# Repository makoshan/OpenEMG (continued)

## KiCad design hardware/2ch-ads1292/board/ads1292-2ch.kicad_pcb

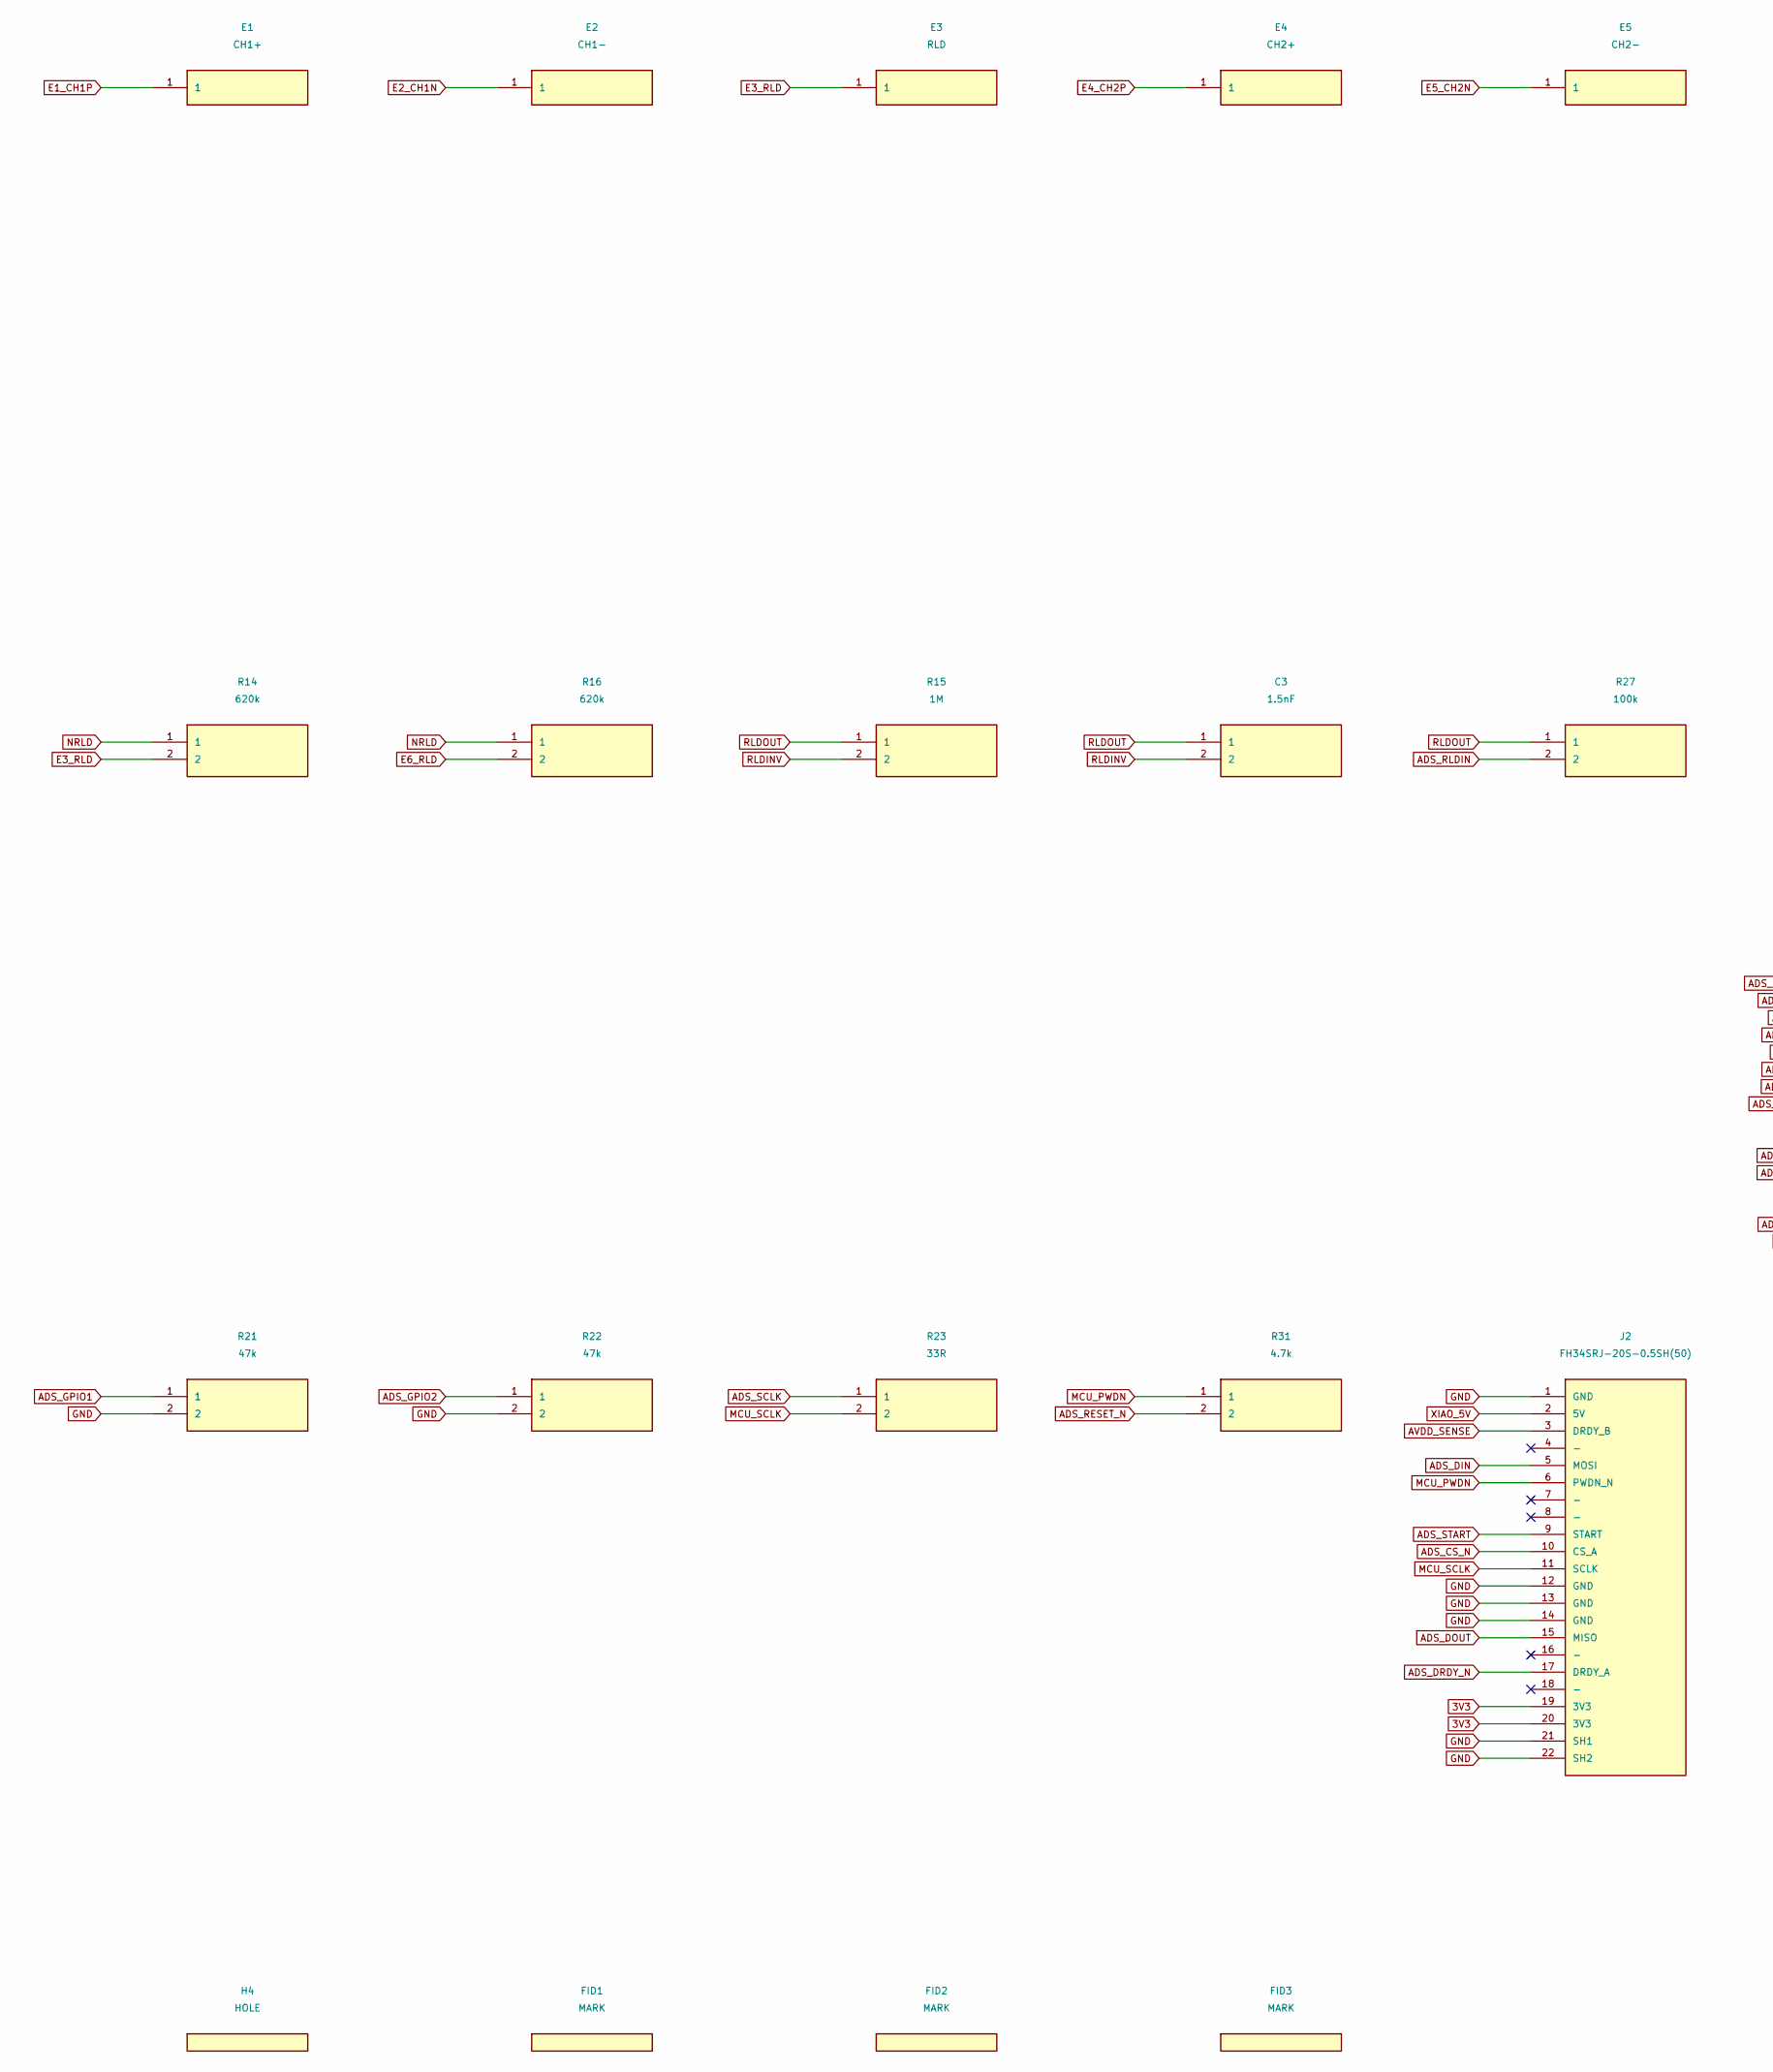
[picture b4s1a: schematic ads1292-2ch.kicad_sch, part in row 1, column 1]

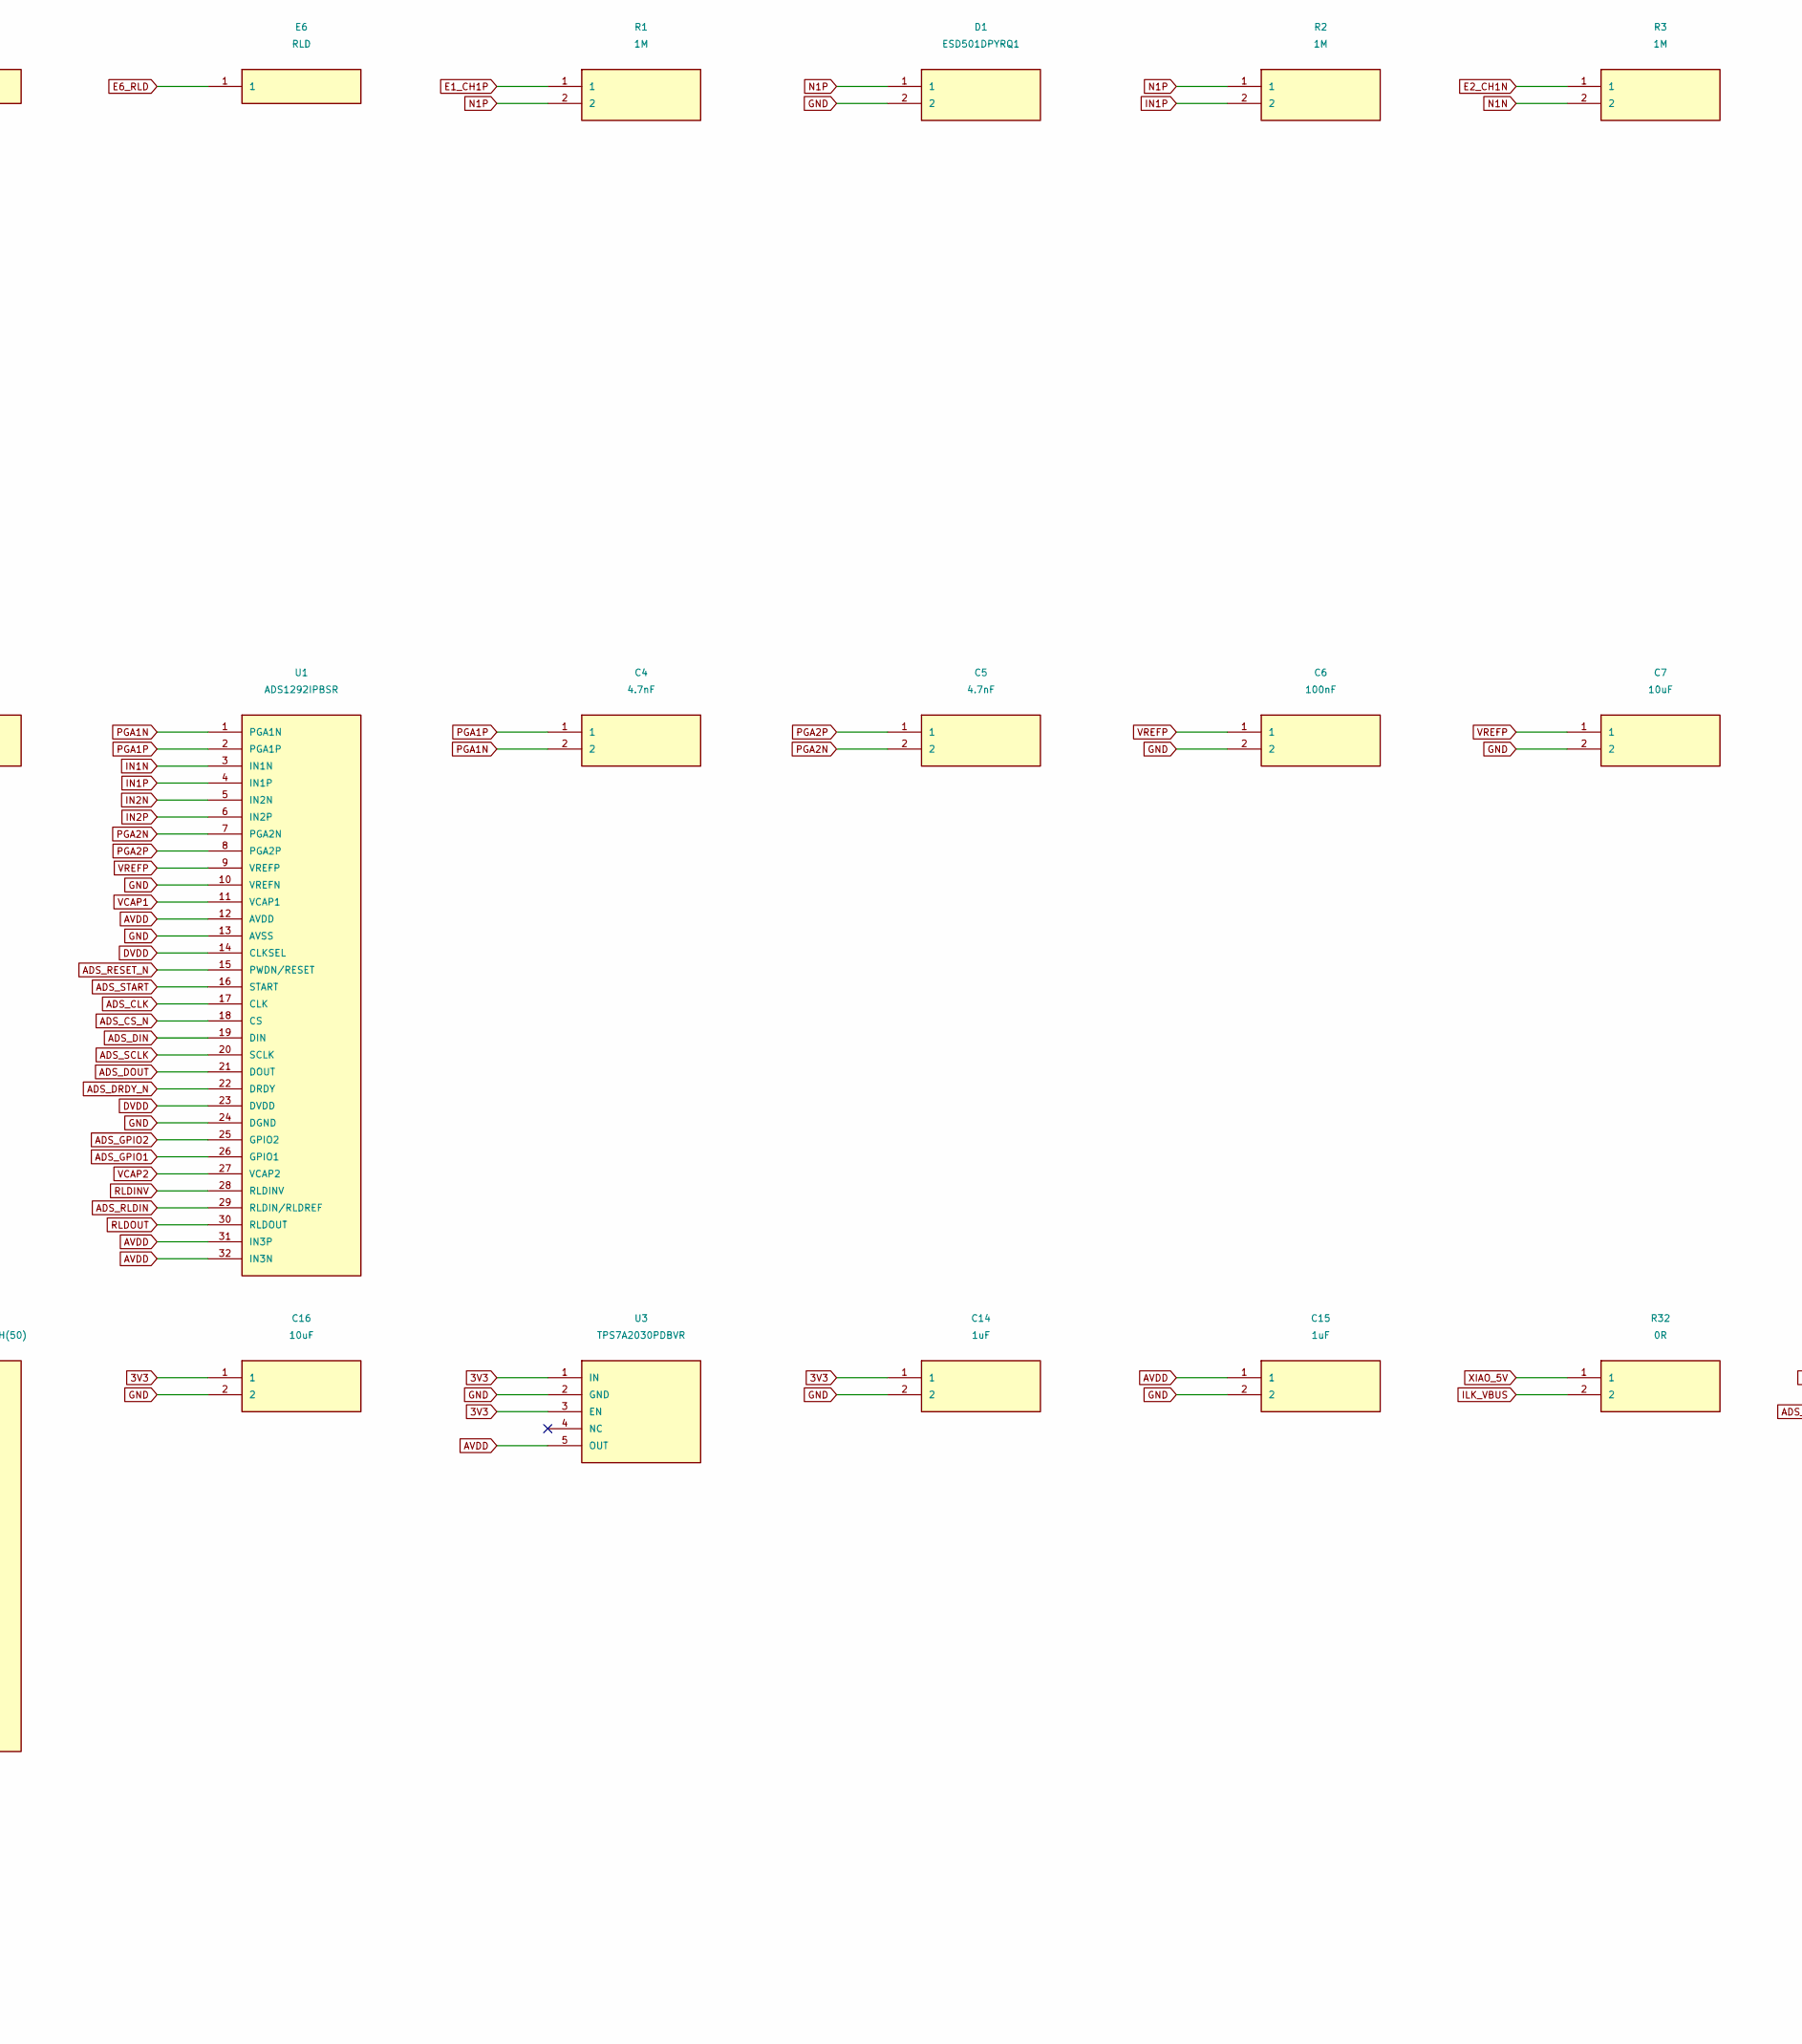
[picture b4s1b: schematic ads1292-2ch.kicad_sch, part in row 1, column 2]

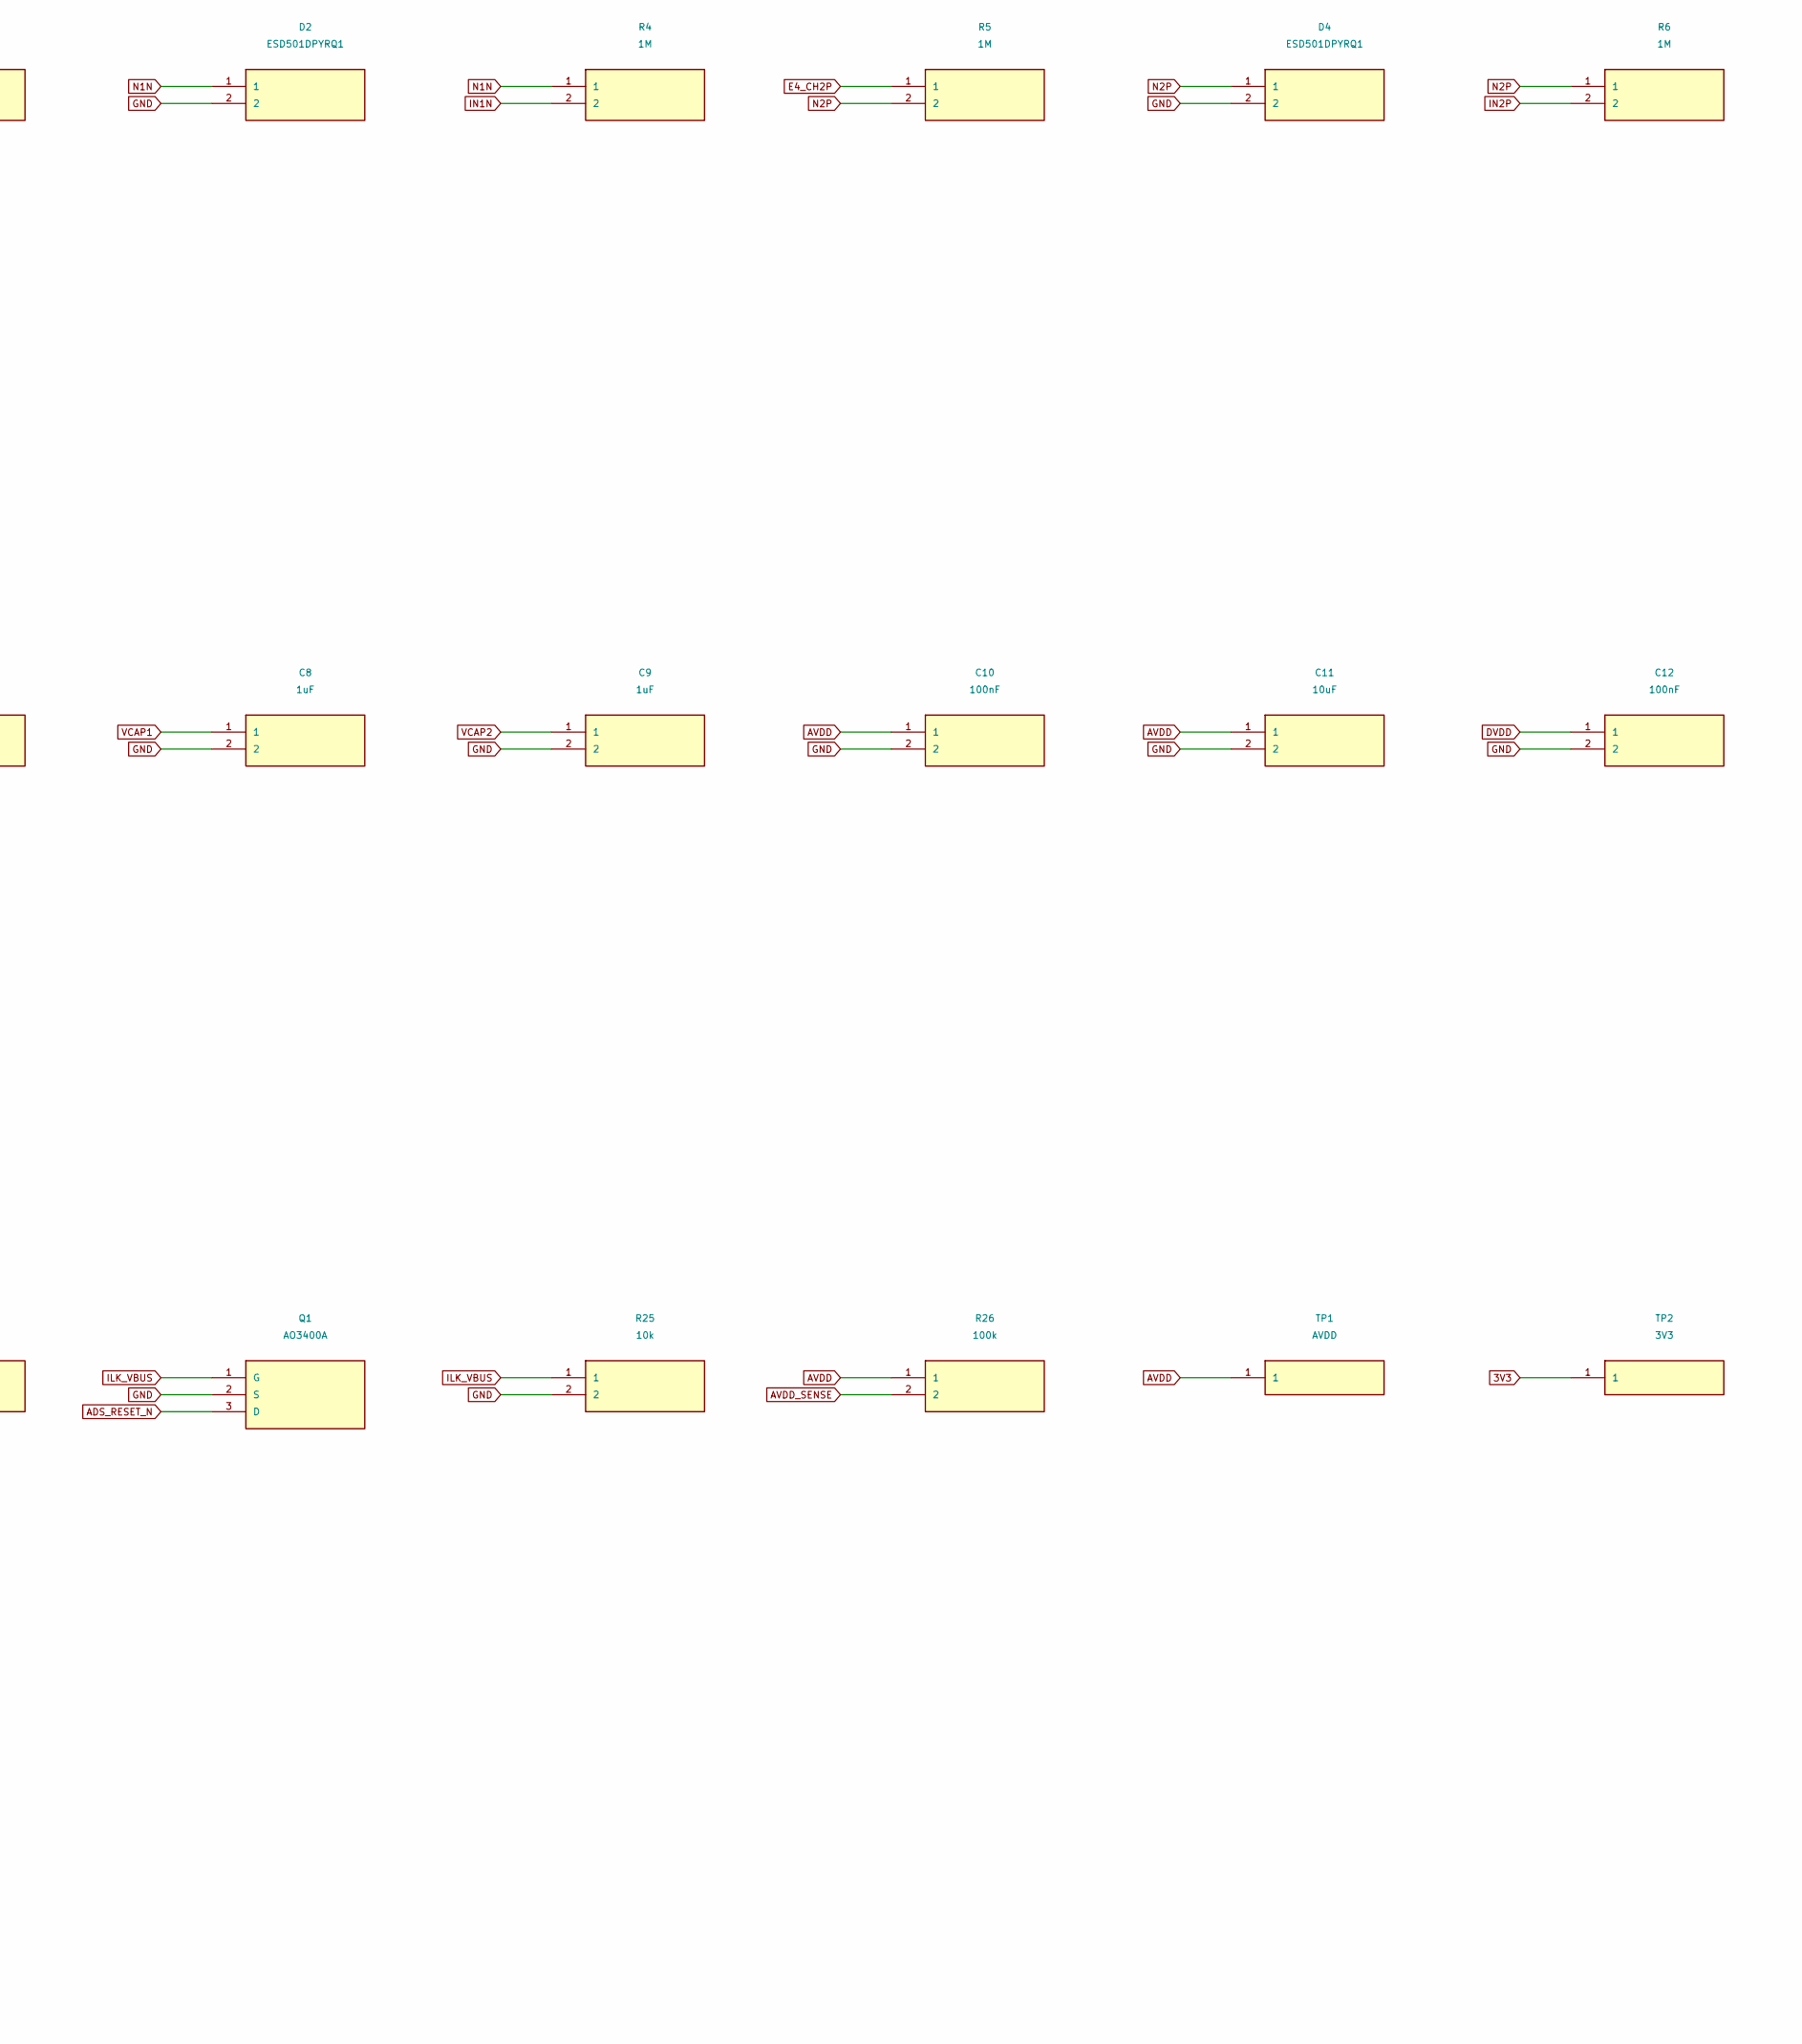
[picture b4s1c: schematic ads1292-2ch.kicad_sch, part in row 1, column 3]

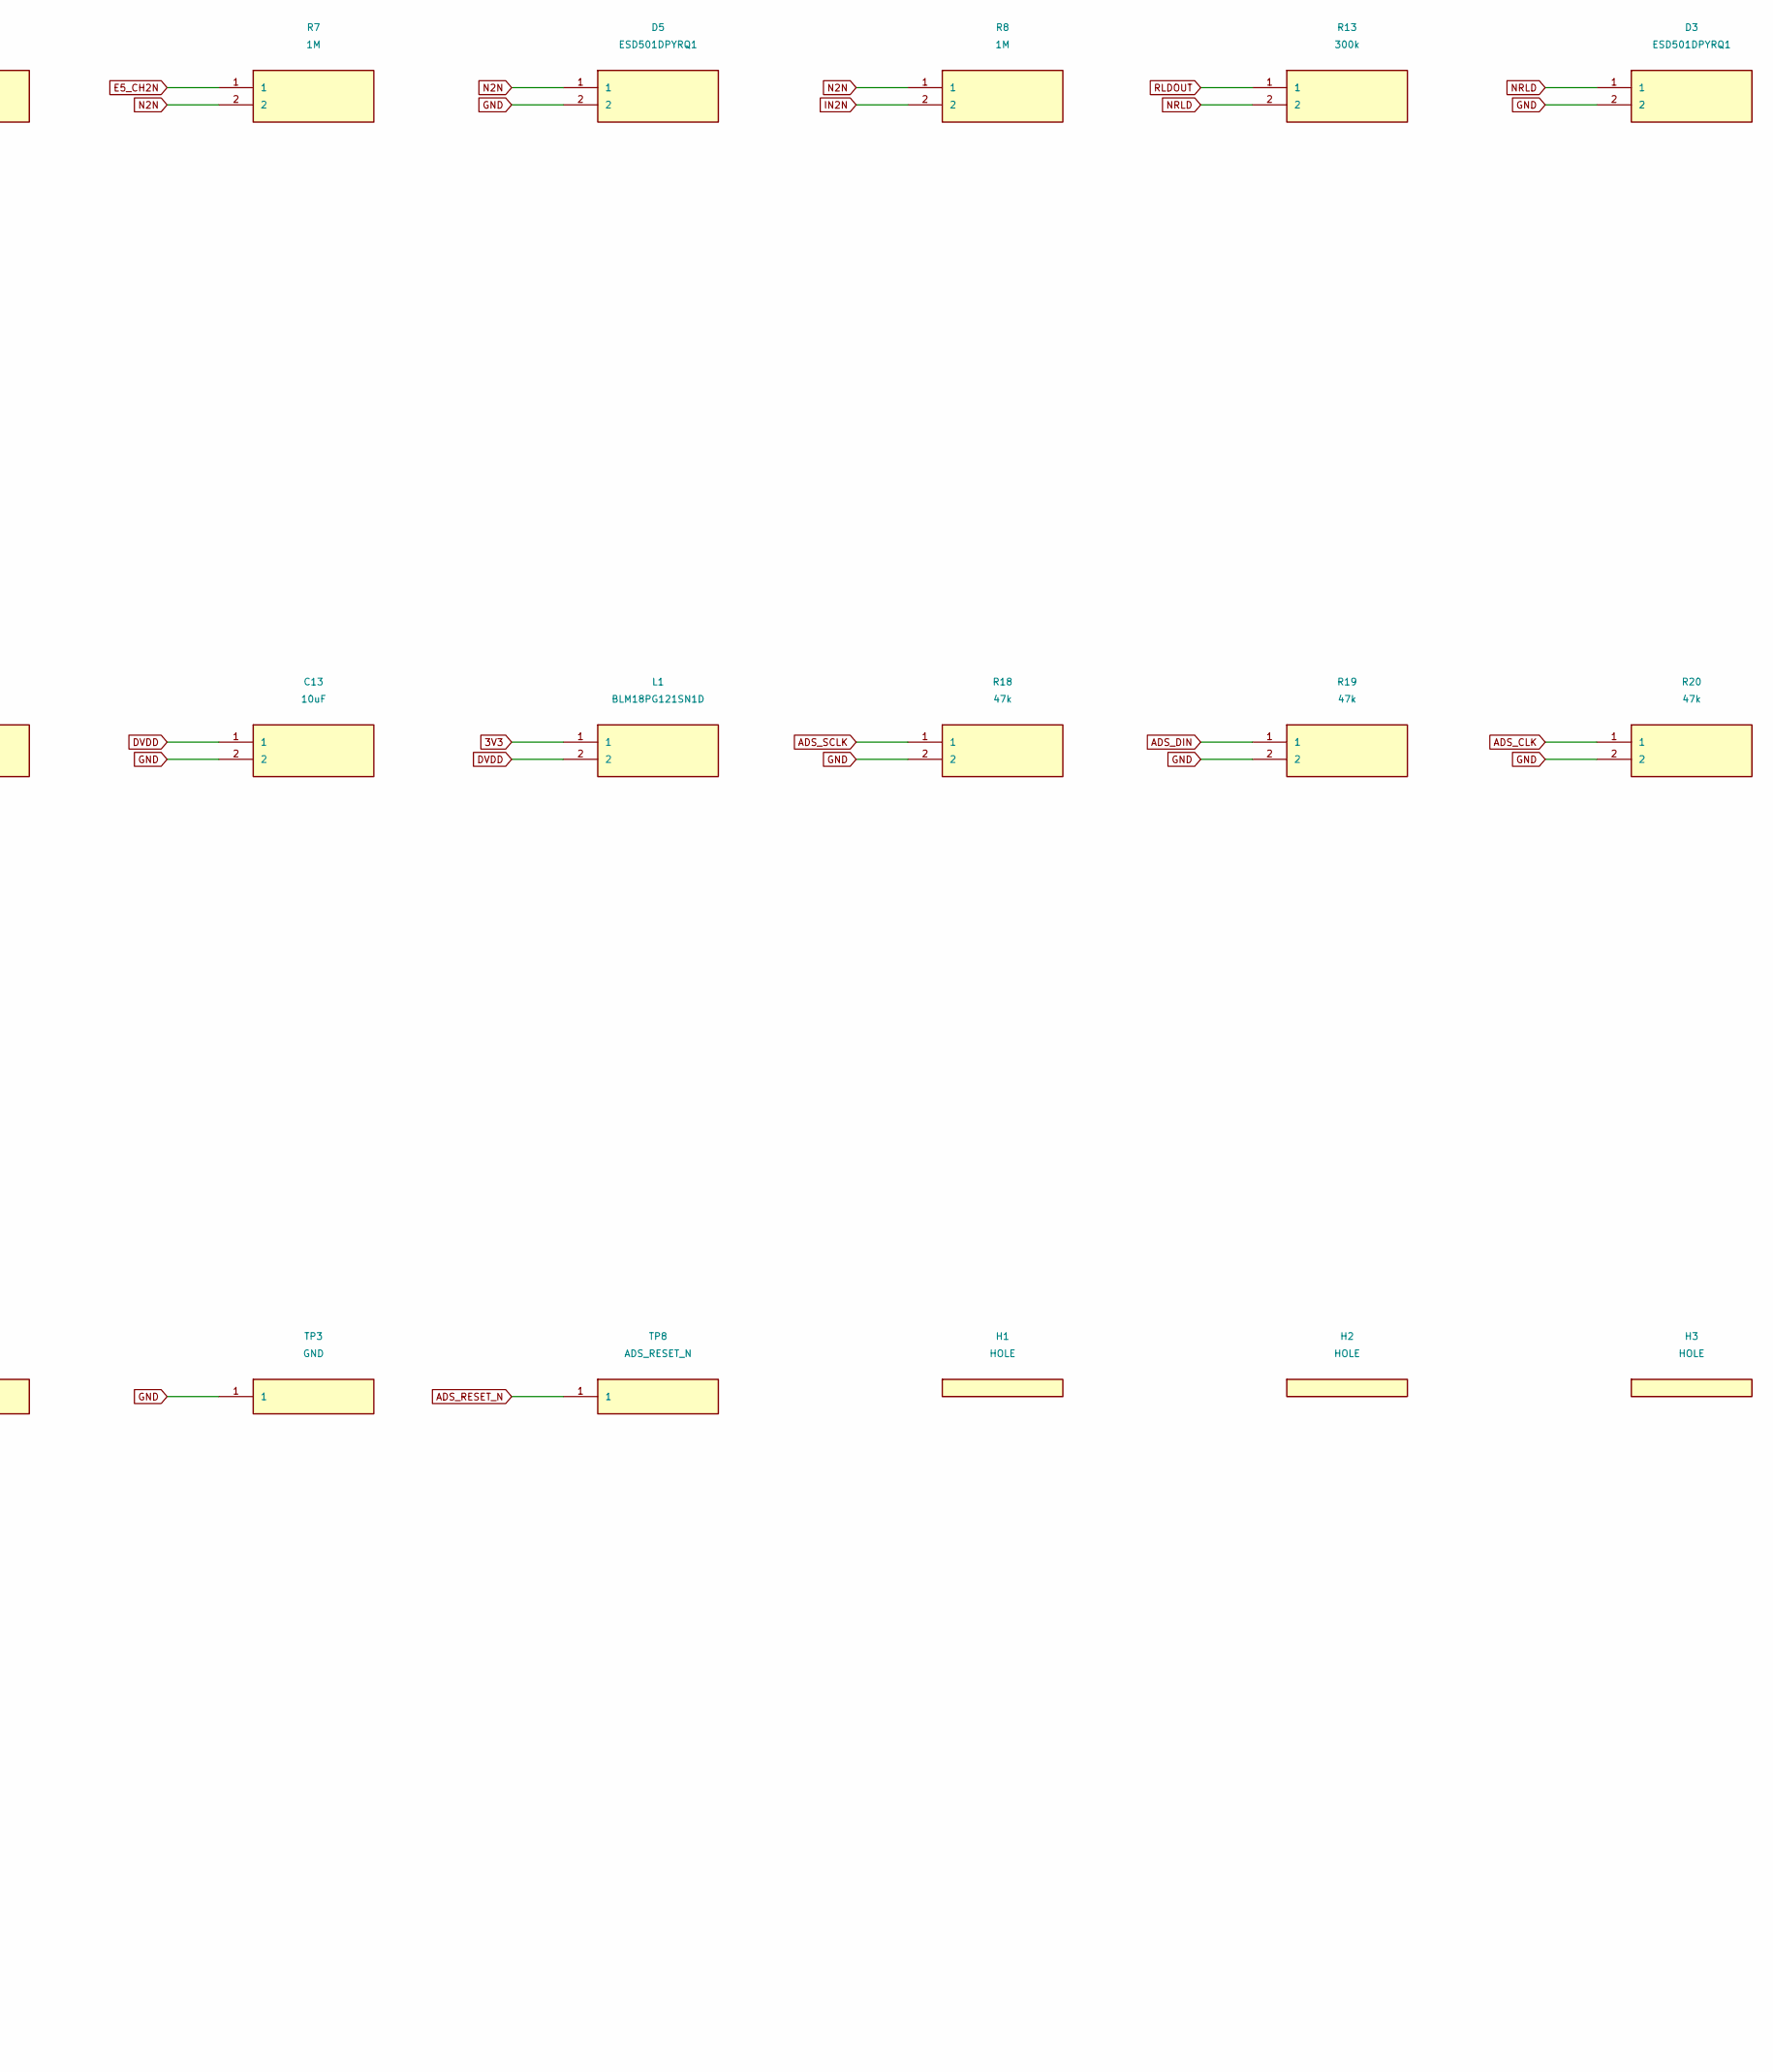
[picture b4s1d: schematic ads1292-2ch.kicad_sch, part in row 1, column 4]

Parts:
C3: 1.5nF; C_0402_1005Metric; LCSC C23967
C4, C5: 4.7nF; C_0402_1005Metric; LCSC C1538
C6, C10, C12: 100nF; C_0402_1005Metric; LCSC C1525
C7, C16: 10uF; C_0603_1608Metric; LCSC C19702
C8, C9, C14, C15: 1uF; C_0402_1005Metric; LCSC C52923
C11, C13: 10uF; C_0402_1005Metric; LCSC C15525
D1, D2, D3, D4, D5: ESD501DPYRQ1; Texas_DPY0002A_0.6x1mm_P0.65mm; LCSC C43177583
E1: CH1+; ELECTRODE_PAD
E2: CH1-; ELECTRODE_PAD
E3, E6: RLD; ELECTRODE_PAD_AUX
E4: CH2+; ELECTRODE_PAD
E5: CH2-; ELECTRODE_PAD
FID1, FID2, FID3: MARK; Fiducial_1mm_Mask2mm
H1, H2, H3, H4: HOLE; HOLE_1P7
J2: FH34SRJ-20S-0.5SH(50); Hirose_FH34SRJ-20S-0.5SH; LCSC C2802370
L1: BLM18PG121SN1D; L_0603_1608Metric; LCSC C14709
Q1: AO3400A; SOT-23; LCSC C20917
R1, R3, R5, R7: 1M; R_0603_1608Metric; LCSC C22935
R2, R4, R6, R8, R15: 1M; R_0402_1005Metric; LCSC C26083
R13: 300k; R_0603_1608Metric; LCSC C23024
R14, R16: 620k; R_0603_1608Metric; LCSC C23219
R18, R19, R20, R21, R22: 47k; R_0402_1005Metric; LCSC C25792
R23: 33R; R_0402_1005Metric; LCSC C25105
R25: 10k; R_0402_1005Metric; LCSC C25744
R26, R27: 100k; R_0402_1005Metric; LCSC C25741
R31: 4.7k; R_0402_1005Metric; LCSC C25900
R32: 0R; R_0402_1005Metric; LCSC C17168
TP1: AVDD; TestPoint_Pad_D1.0mm
TP2: 3V3; TestPoint_Pad_D1.0mm
TP3: GND; TestPoint_Pad_D1.0mm
TP8: ADS_RESET_N; TestPoint_Pad_D1.0mm
U1: ADS1292IPBSR; TQFP-32_5x5mm_P0.5mm; LCSC C2651570
U3: TPS7A2030PDBVR; SOT-23-5; LCSC C963429

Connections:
3V3: C14.1, C16.1, J2.19 (3V3), J2.20 (3V3), L1.1, TP2.1, U3.1 (IN), U3.3 (EN)
ADS_CLK: R20.1, U1.17 (CLK)
ADS_CS_N: J2.10 (CS_A), U1.18 (CS)
ADS_DIN: J2.5 (MOSI), R19.1, U1.19 (DIN)
ADS_DOUT: J2.15 (MISO), U1.21 (DOUT)
ADS_DRDY_N: J2.17 (DRDY_A), U1.22 (DRDY)
ADS_GPIO1: R21.1, U1.26 (GPIO1)
ADS_GPIO2: R22.1, U1.25 (GPIO2)
ADS_RESET_N: Q1.3 (D), R31.2, TP8.1, U1.15 (PWDN/RESET)
ADS_RLDIN: R27.2, U1.29 (RLDIN/RLDREF)
ADS_SCLK: R18.1, R23.1, U1.20 (SCLK)
ADS_START: J2.9 (START), U1.16 (START)
AVDD: C10.1, C11.1, C15.1, R26.1, TP1.1, U1.12 (AVDD), U1.31 (IN3P), U1.32 (IN3N), U3.5 (OUT)
AVDD_SENSE: J2.3 (DRDY_B), R26.2
DVDD: C12.1, C13.1, L1.2, U1.14 (CLKSEL), U1.23 (DVDD)
E1_CH1P: E1.1, R1.1
E2_CH1N: E2.1, R3.1
E3_RLD: E3.1, R14.2
E4_CH2P: E4.1, R5.1
E5_CH2N: E5.1, R7.1
E6_RLD: E6.1, R16.2
GND: C6.2, C7.2, C8.2, C9.2, C10.2, C11.2, C12.2, C13.2, C14.2, C15.2, C16.2, D1.2, D2.2, D3.2, D4.2, D5.2, J2.1 (GND), J2.12 (GND), J2.13 (GND), J2.14 (GND), J2.21 (SH1), J2.22 (SH2), Q1.2 (S), R18.2, R19.2, R20.2, R21.2, R22.2, R25.2, TP3.1, U1.10 (VREFN), U1.13 (AVSS), U1.24 (DGND), U3.2 (GND)
ILK_VBUS: Q1.1 (G), R25.1, R32.2
IN1N: R4.2, U1.3 (IN1N)
IN1P: R2.2, U1.4 (IN1P)
IN2N: R8.2, U1.5 (IN2N)
IN2P: R6.2, U1.6 (IN2P)
MCU_PWDN: J2.6 (PWDN_N), R31.1
MCU_SCLK: J2.11 (SCLK), R23.2
N1N: D2.1, R3.2, R4.1
N1P: D1.1, R1.2, R2.1
N2N: D5.1, R7.2, R8.1
N2P: D4.1, R5.2, R6.1
NRLD: D3.1, R13.2, R14.1, R16.1
PGA1N: C4.2, U1.1 (PGA1N)
PGA1P: C4.1, U1.2 (PGA1P)
PGA2N: C5.2, U1.7 (PGA2N)
PGA2P: C5.1, U1.8 (PGA2P)
RLDINV: C3.2, R15.2, U1.28 (RLDINV)
RLDOUT: C3.1, R13.1, R15.1, R27.1, U1.30 (RLDOUT)
VCAP1: C8.1, U1.11 (VCAP1)
VCAP2: C9.1, U1.27 (VCAP2)
VREFP: C6.1, C7.1, U1.9 (VREFP)
XIAO_5V: J2.2 (5V), R32.1

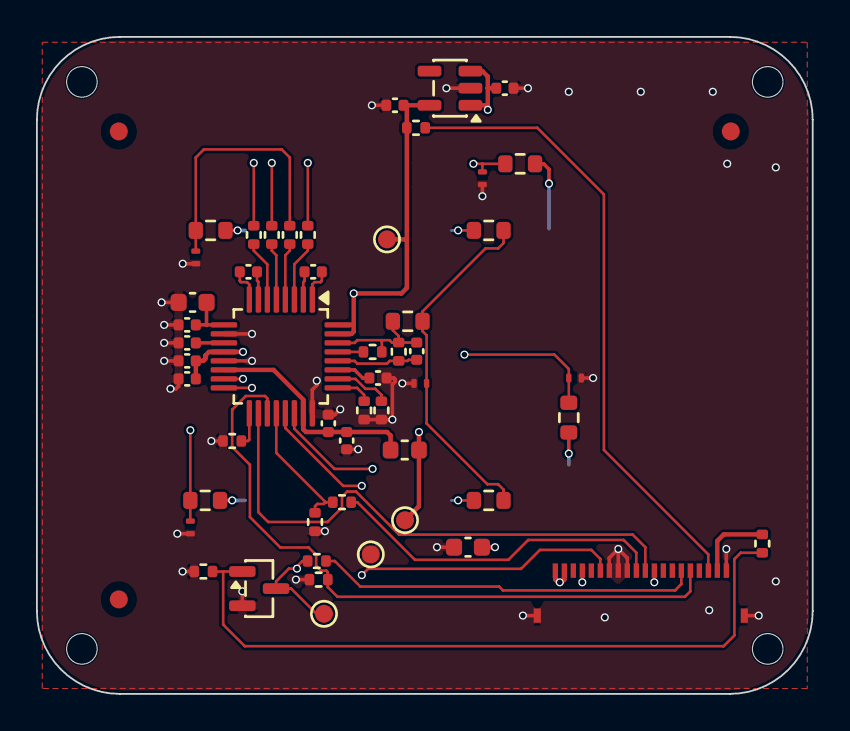
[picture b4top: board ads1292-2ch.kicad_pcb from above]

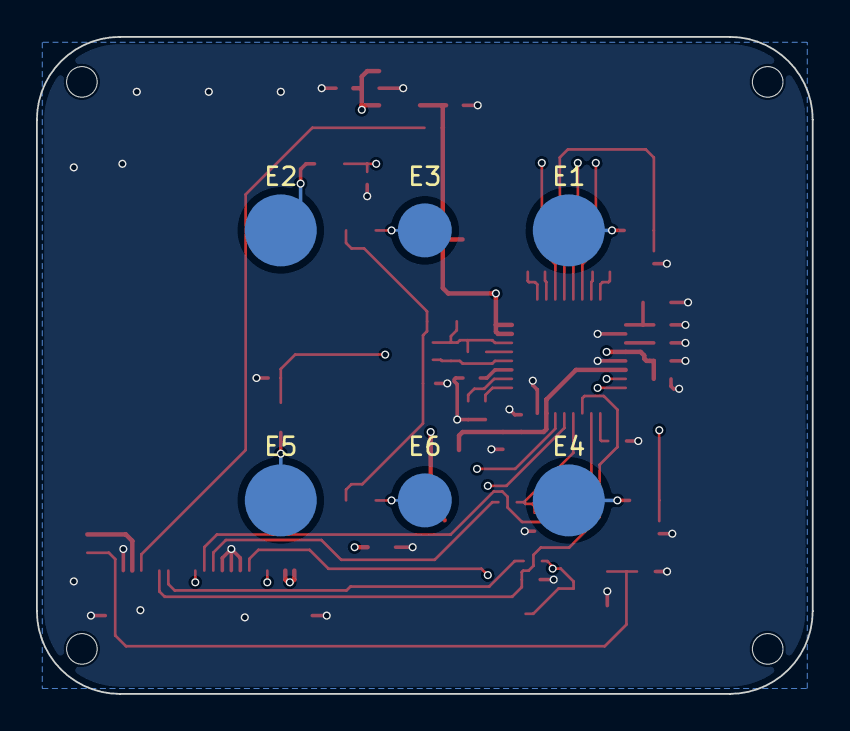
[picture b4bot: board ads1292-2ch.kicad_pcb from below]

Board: 4 copper layers, 43.1 x 36.5 mm, 64 parts (6 on the bottom side), 44 nets.

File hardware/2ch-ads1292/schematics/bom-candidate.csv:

位号,值,封装,LCSC,首版
E1,CH1+,ads:ELECTRODE_PAD,,贴
E2,CH1-,ads:ELECTRODE_PAD,,贴
E3,RLD,ads:ELECTRODE_PAD_AUX,,贴
E4,CH2+,ads:ELECTRODE_PAD,,贴
E5,CH2-,ads:ELECTRODE_PAD,,贴
E6,RLD,ads:ELECTRODE_PAD_AUX,,贴
R1,1M,Resistor_SMD:R_0603_1608Metric,C22935,贴
D1,ESD501DPYRQ1,Package_SON:Texas_DPY0002A_0.6x1mm_P0.65mm,C43177583,贴
R2,1M,Resistor_SMD:R_0402_1005Metric,C26083,贴
R3,1M,Resistor_SMD:R_0603_1608Metric,C22935,贴
D2,ESD501DPYRQ1,Package_SON:Texas_DPY0002A_0.6x1mm_P0.65mm,C43177583,贴
R4,1M,Resistor_SMD:R_0402_1005Metric,C26083,贴
R5,1M,Resistor_SMD:R_0603_1608Metric,C22935,贴
D4,ESD501DPYRQ1,Package_SON:Texas_DPY0002A_0.6x1mm_P0.65mm,C43177583,贴
R6,1M,Resistor_SMD:R_0402_1005Metric,C26083,贴
R7,1M,Resistor_SMD:R_0603_1608Metric,C22935,贴
D5,ESD501DPYRQ1,Package_SON:Texas_DPY0002A_0.6x1mm_P0.65mm,C43177583,贴
R8,1M,Resistor_SMD:R_0402_1005Metric,C26083,贴
R13,300k,Resistor_SMD:R_0603_1608Metric,C23024,贴
D3,ESD501DPYRQ1,Package_SON:Texas_DPY0002A_0.6x1mm_P0.65mm,C43177583,贴
R14,620k,Resistor_SMD:R_0603_1608Metric,C23219,贴
R16,620k,Resistor_SMD:R_0603_1608Metric,C23219,贴
R15,1M,Resistor_SMD:R_0402_1005Metric,C26083,贴
C3,1.5nF,Capacitor_SMD:C_0402_1005Metric,C23967,贴
R27,100k,Resistor_SMD:R_0402_1005Metric,C25741,贴
U1,ADS1292IPBSR,Package_QFP:TQFP-32_5x5mm_P0.5mm,C2651570,贴
C4,4.7nF,Capacitor_SMD:C_0402_1005Metric,C1538,贴
C5,4.7nF,Capacitor_SMD:C_0402_1005Metric,C1538,贴
C6,100nF,Capacitor_SMD:C_0402_1005Metric,C1525,贴
C7,10uF,Capacitor_SMD:C_0603_1608Metric,C19702,贴
C8,1uF,Capacitor_SMD:C_0402_1005Metric,C52923,贴
C9,1uF,Capacitor_SMD:C_0402_1005Metric,C52923,贴
C10,100nF,Capacitor_SMD:C_0402_1005Metric,C1525,贴
C11,10uF,Capacitor_SMD:C_0402_1005Metric,C15525,贴
C12,100nF,Capacitor_SMD:C_0402_1005Metric,C1525,贴
C13,10uF,Capacitor_SMD:C_0402_1005Metric,C15525,贴
L1,BLM18PG121SN1D,Inductor_SMD:L_0603_1608Metric,C14709,贴
R18,47k,Resistor_SMD:R_0402_1005Metric,C25792,贴
R19,47k,Resistor_SMD:R_0402_1005Metric,C25792,贴
R20,47k,Resistor_SMD:R_0402_1005Metric,C25792,贴
R21,47k,Resistor_SMD:R_0402_1005Metric,C25792,贴
R22,47k,Resistor_SMD:R_0402_1005Metric,C25792,贴
R23,33R,Resistor_SMD:R_0402_1005Metric,C25105,贴
R31,4.7k,Resistor_SMD:R_0402_1005Metric,C25900,贴
J2,FH34SRJ-20S-0.5SH(50),p44:Hirose_FH34SRJ-20S-0.5SH,C2802370,贴
C16,10uF,Capacitor_SMD:C_0603_1608Metric,C19702,贴
U3,TPS7A2030PDBVR,Package_TO_SOT_SMD:SOT-23-5,C963429,贴
C14,1uF,Capacitor_SMD:C_0402_1005Metric,C52923,贴
C15,1uF,Capacitor_SMD:C_0402_1005Metric,C52923,贴
R32,0R,Resistor_SMD:R_0402_1005Metric,C17168,贴
Q1,AO3400A,Package_TO_SOT_SMD:SOT-23,C20917,贴
R25,10k,Resistor_SMD:R_0402_1005Metric,C25744,贴
R26,100k,Resistor_SMD:R_0402_1005Metric,C25741,贴
TP1,AVDD,TestPoint:TestPoint_Pad_D1.0mm,,贴
TP2,3V3,TestPoint:TestPoint_Pad_D1.0mm,,贴
TP3,GND,TestPoint:TestPoint_Pad_D1.0mm,,贴
TP8,ADS_RESET_N,TestPoint:TestPoint_Pad_D1.0mm,,贴
H1,HOLE,ads:HOLE_1P7,,贴
H2,HOLE,ads:HOLE_1P7,,贴
H3,HOLE,ads:HOLE_1P7,,贴
H4,HOLE,ads:HOLE_1P7,,贴
FID1,MARK,Fiducial:Fiducial_1mm_Mask2mm,,贴
FID2,MARK,Fiducial:Fiducial_1mm_Mask2mm,,贴
FID3,MARK,Fiducial:Fiducial_1mm_Mask2mm,,贴
